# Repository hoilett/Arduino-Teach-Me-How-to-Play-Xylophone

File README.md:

# Arduino-Teach-Me-How-to-Play-Xylophone

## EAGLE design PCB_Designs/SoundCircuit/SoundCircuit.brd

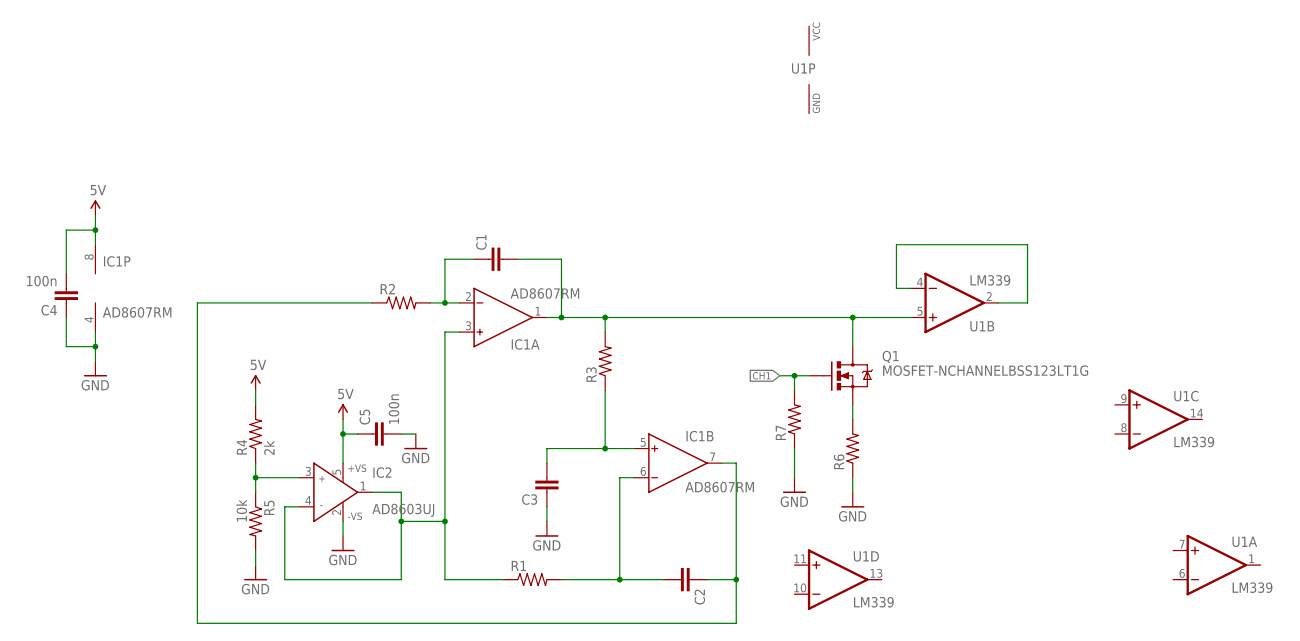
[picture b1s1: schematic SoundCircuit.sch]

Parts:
C1, C2, C3: C-EUC0402; C0402
C4, C5: 100n; C0402
IC1: AD8607RM; MSOP08
IC2: AD8603UJ; SOT23-5
Q1: MOSFET-NCHANNELBSS123LT1G; SOT23-3
R1, R2, R3, R6, R7: R-US_R0402; R0402
R4: 2k; R0402
R5: 10k; R0402
U1: LM339; TSSOP-14

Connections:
5V: C4.2, C5.1, IC1.8 (V+), IC2.5 (+VS), R4.2
CH1: Q1.1 (G), R7.2
GND: C3.1, C4.1, C5.2, IC1.4 (V-), IC2.2 (-VS), R5.2, R6.1, R7.1, U1.12 (GND)
unnamed: C1.2, IC1.1 (OUT), Q1.3 (D), R3.2, U1.5 (+IN)
unnamed: C3.2, IC1.5 (IN+), R3.1
unnamed: C1.1, IC1.2 (IN-), R2.2
unnamed: C2.1, IC1.7 (OUT), R2.1
unnamed: C2.2, IC1.6 (IN-), R1.2
unnamed: IC1.3 (IN+), IC2.1 (OUT), IC2.4 (IN-), R1.1
unnamed: IC2.3 (IN+), R4.1, R5.1
unnamed: U1.2 (OUT), U1.4 (-IN)
unnamed: Q1.2 (S), R6.2
VCC: U1.3 (VCC)

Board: 2 copper layers, 16 parts (12 on the bottom side), 12 nets, no tracks yet.

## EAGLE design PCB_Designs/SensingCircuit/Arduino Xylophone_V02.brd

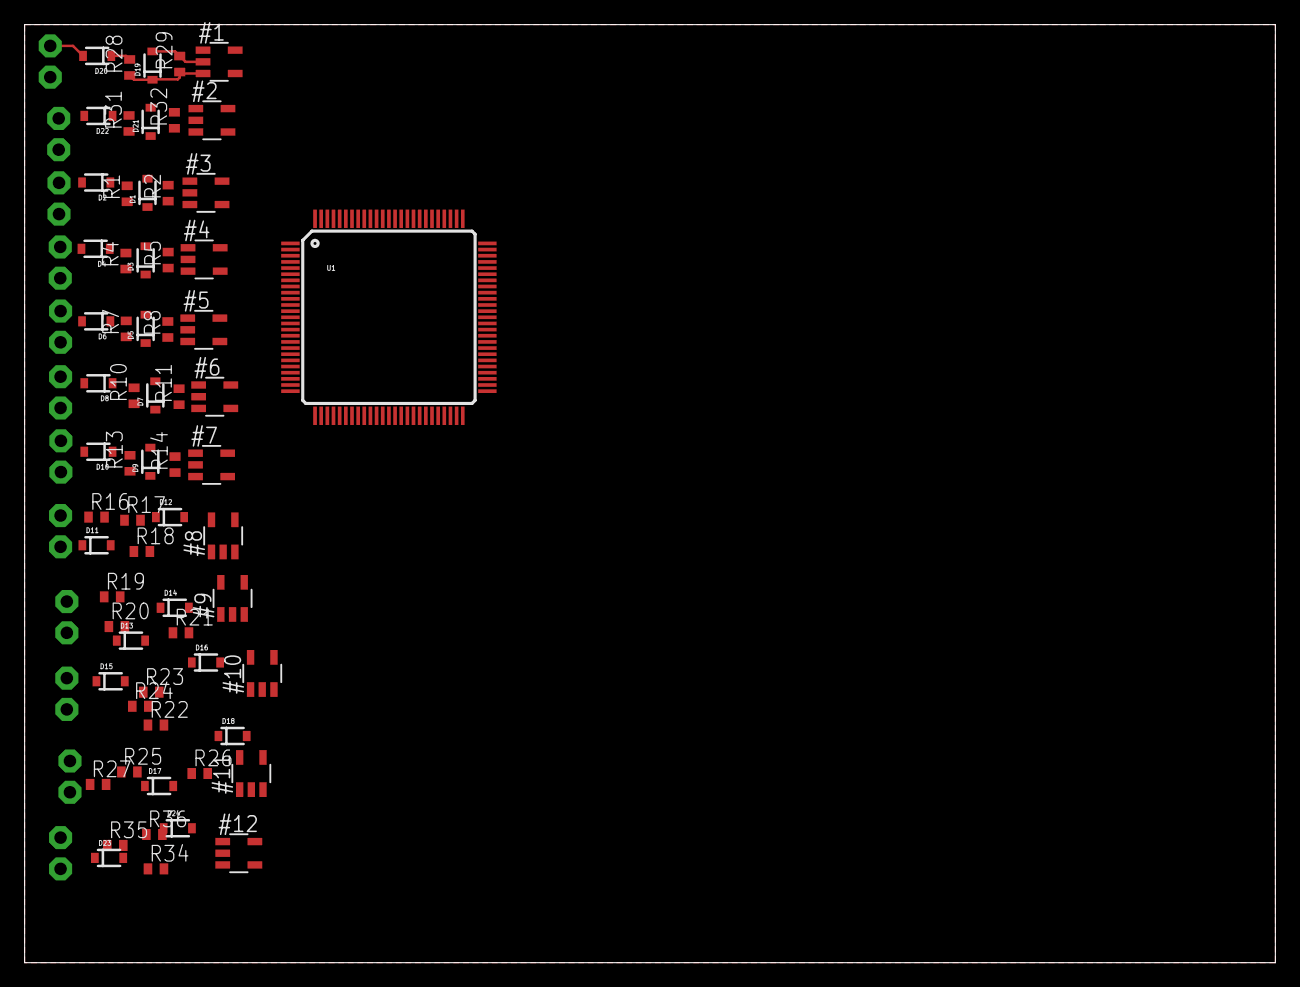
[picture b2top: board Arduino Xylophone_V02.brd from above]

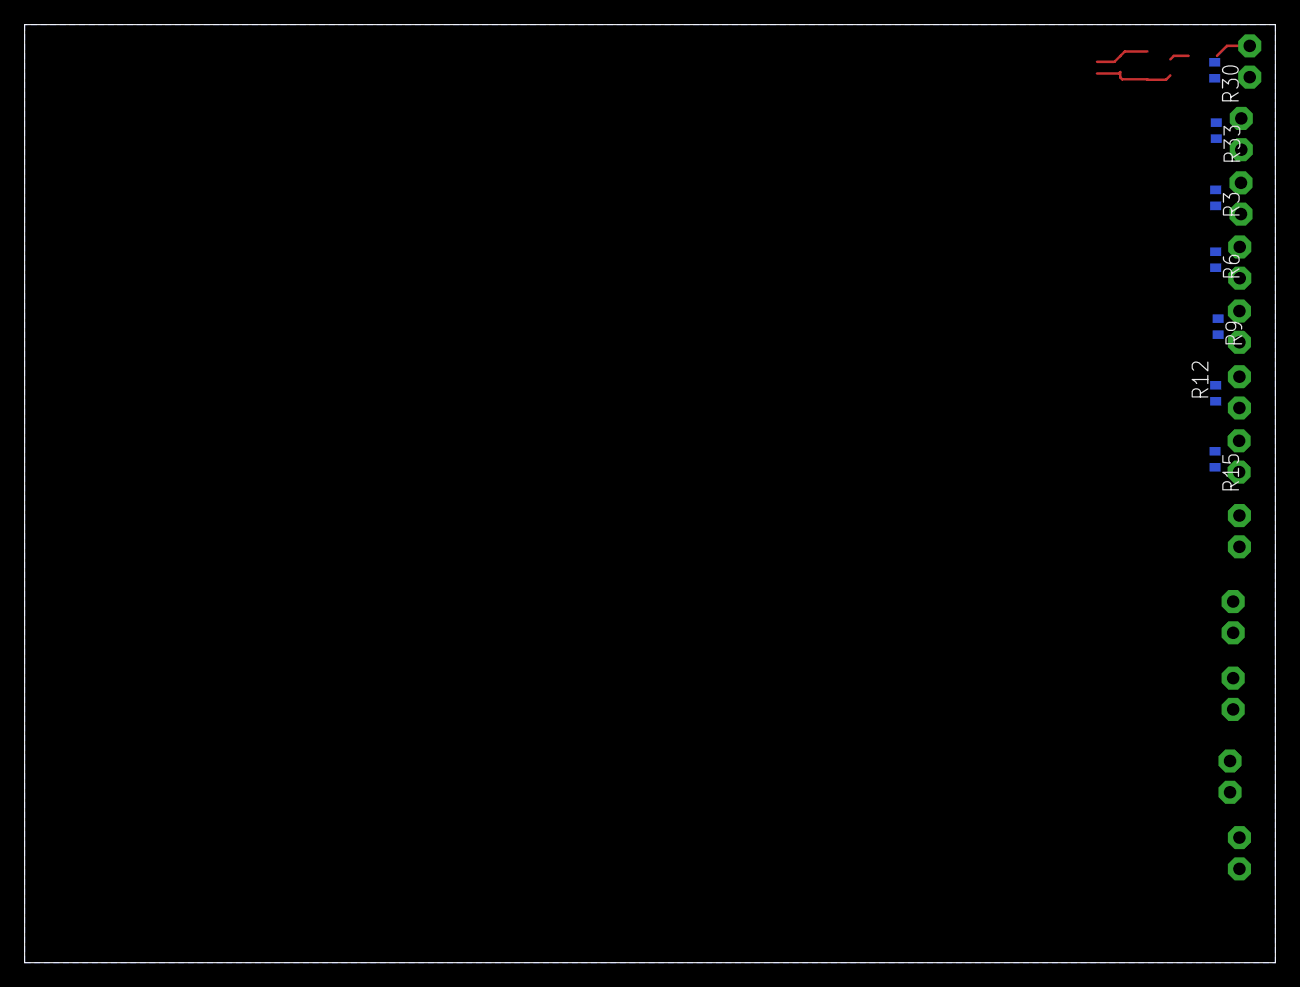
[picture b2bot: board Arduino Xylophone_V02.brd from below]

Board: 2 copper layers, 101.6 x 76.2 mm, 85 parts (7 on the bottom side), 50 nets.

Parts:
#1, #2, #3, #4, #5, #6, #7, #8, #9, #10, #11, #12: MCP601OT; SOT23-5
D1, D3, D5, D7, D9, D11, D13, D15, D17, D19, D21, D23: 3.3V; SOD-323
D2, D4, D6, D8, D10, D12, D14, D16, D18, D20, D22, D24: 250mA/100V; SOD-323
P-1, P-2, P-3, P-4, P-5, P-6, P-7, P-8, P-9, P-10, P-11, P-12: PIEZO; VIA
R1, R2, R3, R4, R5, R6, R7, R8, R9, R10, R11, R12, R13, R14, R15, R16, R17, R18, R19, R20, R21, R22, R23, R24, R25, R26, R27, R28, R29, R30, R31, R32, R33, R34, R35, R36: R0402
U1: ATMEGA2560AU; TQFP100

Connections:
5V: #1.5, #2.5, #3.5, #4.5, #5.5, #6.5, #7.5, #8.5, #9.5, #10.5, #11.5, #12.5
GND: #1.2, #2.2, #3.2, #4.2, #5.2, #6.2, #7.2, #8.2, #9.2, #10.2, #11.2, #12.2, D1.A, D3.A, D5.A, D7.A, D9.A, D11.A, D13.A, D15.A, D17.A, D19.A, D21.A, D23.A, P-1.1, P-2.1, P-3.1, P-4.1, P-5.1, P-6.1, P-7.1, P-8.1, P-9.1, P-10.1, P-11.1, P-12.1, R2.2, R3.2, R5.2, R6.2, R8.2, R9.2, R11.2, R12.2, R14.2, R15.2, R17.2, R18.2, R20.2, R21.2, R23.2, R24.2, R26.2, R27.2, R29.2, R30.2, R32.2, R33.2, R35.2, R36.2, U1.11
unnamed: #3.3, D1.C, R1.1, R2.1
unnamed: D2.C, R1.2
unnamed: #3.1, #3.4
unnamed: D2.A, P-1.2, R3.1
unnamed: #4.3, D3.C, R4.1, R5.1
unnamed: D4.C, R4.2
unnamed: #4.1, #4.4
unnamed: D4.A, P-2.2, R6.1
unnamed: #5.3, D5.C, R7.1, R8.1
unnamed: D6.C, R7.2
unnamed: #5.1, #5.4
unnamed: D6.A, P-3.2, R9.1
unnamed: #6.3, D7.C, R10.1, R11.1
unnamed: D8.C, R10.2
unnamed: #6.1, #6.4
unnamed: D8.A, P-4.2, R12.1
unnamed: #7.3, D9.C, R13.1, R14.1
unnamed: D10.C, R13.2
unnamed: #7.1, #7.4
unnamed: D10.A, P-5.2, R15.1
unnamed: #8.3, D11.C, R16.1, R17.1
unnamed: D12.C, R16.2
unnamed: #8.1, #8.4
unnamed: D12.A, P-6.2, R18.1
unnamed: #9.3, D13.C, R19.1, R20.1
unnamed: D14.C, R19.2
unnamed: #9.1, #9.4
unnamed: D14.A, P-7.2, R21.1
unnamed: #10.3, D15.C, R22.1, R23.1
unnamed: D16.C, R22.2
unnamed: #10.1, #10.4
unnamed: D16.A, P-8.2, R24.1
unnamed: #11.3, D17.C, R25.1, R26.1
unnamed: D18.C, R25.2
unnamed: #11.1, #11.4
unnamed: D18.A, P-9.2, R27.1
unnamed: #1.3, D19.C, R28.1, R29.1
unnamed: D20.C, R28.2
unnamed: #1.1, #1.4
unnamed: D20.A, P-10.2, R30.1
unnamed: #2.3, D21.C, R31.1, R32.1
unnamed: D22.C, R31.2
unnamed: #2.1, #2.4
unnamed: D22.A, P-11.2, R33.1
unnamed: #12.3, D23.C, R34.1, R35.1
unnamed: D24.C, R34.2
unnamed: #12.1, #12.4
unnamed: D24.A, P-12.2, R36.1

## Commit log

2016-03-09 source definition file for Xylophone class
2016-03-09 class declaration fiile for Xylophone class
2016-03-09 .ino file for xylophone project
2016-03-12 working on Xylophone class
2016-03-28 adding the PCB design files to GitHub
2016-03-29 working on board layout for Xylophone sensing circuit
2016-05-02 changed file name of pcb designs
2016-05-04 sine wave generator for sound circuit
2016-05-14 added some more datasheets

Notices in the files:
parts and their libraries:
SparkFun-DiscreteSemi: Licensing: Creative Commons ShareAlike 4.0 International - https://creativecommons.org/licenses/by-sa/4.0
